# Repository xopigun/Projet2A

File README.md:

# Projet 2A — Bus CAN, groupe 69

ENSEA 2A, projet « Conception d'une Électronique Modulaire (Bus CAN) ».
Auteurs (ordre alphabétique) : Samuel GOMRI, Dylan KIATI, Hugo MATHOUX.

**Où en est le projet : [banc-can/docs/ETAT_PROJET.md](banc-can/docs/ETAT_PROJET.md).**

| Dossier | Contenu |
|---|---|
| [`banc-can/`](banc-can/README.md) | Le banc de test : firmwares des nœuds, ICD, outils PC `canbench`, cartes KiCad (adaptateur USB-CAN, carte porteuse, câblage), simulation 3D, documentation |
| `Banc de Test/` | Dossier de définition du banc (source LaTeX et PDF) |
| `ICD/` | Formulaire ICD commun aux groupes partenaires |
| `Cobot/` | Schéma du bus CAN du Cobot |
| `GANTT/` | Planning détaillé (LaTeX) |
| `Management/` | Notes de pré-cadrage, RACI, registre des risques, plannings, macroplanning |

Cloner avec les sous-modules du firmware :

```bash
git clone --recursive https://github.com/xopigun/Projet2A.git
```

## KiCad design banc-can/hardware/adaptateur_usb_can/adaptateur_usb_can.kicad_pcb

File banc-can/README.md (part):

# Banc de test CAN — G69-BANC-001

Outil interne du **groupe 69** (ENSEA 2A, projet « Conception d'une Électronique Modulaire
(Bus CAN) ») servant à valider le standard CAN commun et les ICD produits avec les groupes
partenaires.

Le banc est **générique** : aucun code n'est spécifique à un groupe partenaire, les besoins
particuliers passent par de la configuration. Les quatre projets partenaires (Cobot RMD-X,
Ecomarathon, Formula Student, MIR1000) sont traités au même niveau.

Auteurs (ordre alphabétique) : Samuel GOMRI, Dylan KIATI, Hugo MATHOUX.

**État du projet, choix abandonnés et prochaines étapes : [docs/ETAT_PROJET.md](docs/ETAT_PROJET.md).**

---

## ⚠ À faire avant la première mise sous tension

Ces deux points sont des **modifications matérielles** sur chaque Nucleo-G431KB. Les ignorer
donne des symptômes qui ressemblent à une panne et non à une erreur de montage.

1. **Retirer le cavalier HW1**, livré fermé entre `CN4` broche 5 (`D2` = PA12) et `CN4`
   broche 4 (`GND`) — UM2397 §5.1 et §6.1. PA12 est `FDCAN1_TX` : laissé à la masse, il
   place le bus en **état dominant permanent** et bloque toute communication.

2. **Souder les ponts SB9 et SB10** pour connecter le quartz 24 MHz. En sortie d'usine la
   carte démarre sur le **HSI** (UM2397 §6.5, Table 9), dont la précision de ±1 % dépasse
   plus du double la tolérance admissible de 0,485 % à 500 kbit/s. Tant que ce n'est pas
   fait, compiler avec `-DBENCH_CLOCK_SOURCE=HSI` : le firmware émet un avertissement à la
   compilation, affiche `HSI - NON VALIDE` sur l'écran et signale le défaut dans son
   heartbeat, et `canbench` refuse alors de prononcer un verdict de réussite.

**Procédure de mise en route pas à pas : [docs/bringup.md](docs/bringup.md).** Elle amène
trois cartes neuves à un bus qui communique, en validant l'horloge, le temps de bit et
l'encodage **avant** tout câblage grâce au bouclage interne du FDCAN.

Brochage, terminaisons et injection de fautes : [docs/pinout.md](docs/pinout.md).

---

## Démarrage rapide

### Prérequis

| Outil | Version | Rôle |
|---|---|---|
| git | ≥ 2.30 | sous-modules |
| CMake | ≥ 3.24 | presets version 6 |
| Ninja | ≥ 1.10 | générateur |
| `arm-none-eabi-gcc` | ≥ 12 | firmwares |
| `gcc` ou `clang` | — | tests unitaires natifs |
| Python | ≥ 3.10 | outils PC et génération depuis l'ICD |
| STM32CubeProgrammer **ou** OpenOCD | — | programmation (facultatif) |

### Cloner

```bash
git clone --recursive <url> banc-can
cd banc-can
```

Si le dépôt a été cloné sans `--recursive` :

```bash
git submodule update --init --recursive
```

### Compiler et exécuter les tests unitaires (aucun matériel)

```bash
cmake --preset host
cmake --build --preset host
ctest --preset host
```

### Compiler un firmware

Un preset par nœud : `n1` à `n4`, quatre Nucleo-G431KB.

```bash
cmake --preset n1
cmake --build --preset n1
```

### Programmer un nœud

```bash
cmake --build --preset n1 --target flash_n1
```

`STM32_Programmer_CLI` et `openocd` sont cherchés dans le `PATH` puis dans les emplacements
d'installation usuels ; le premier trouvé est utilisé. Pour forcer :
`cmake --preset n1 -DBENCH_FLASH_TOOL=openocd`.

**Plusieurs cartes branchées à la fois** : sans autre précision, l'outil programme la
première sonde trouvée, pas forcément le nœud visé. Lister les sondes, puis fixer une fois
pour toutes le numéro de série de chaque nœud :

```bash
STM32_Programmer_CLI --list st-link
```

```bash
cmake --preset n1-scope-direct -DBENCH_STLINK_SN=005000463335510433383531
```

### Installer les outils PC

```bash
python -m pip install -e "pc[dev]"
```

### Premier test, sans matériel

Toutes les sous-commandes fonctionnent sur le bus `virtual` de python-can, avec un
simulateur qui reproduit N1 à N4 (ARM/GO et heartbeat compris) :

```bash
canbench --interface virtual --simulate arbitration --cycles 100
canbench --interface virtual --simulate encoding
canbench --interface virtual --simulate faults
canbench --interface virtual --simulate busload --measure 2
```

`--simulate` démarre un simulateur reproduisant N1 à N4. **Aucun verdict de réussite n'est
prononcé sur le bus virtuel** : le simulateur reproduit le comportement attendu, il ne le
démontre pas. Les rapports produits portent la mention correspondante.

### Interface graphique

Pour une démonstration, ou simplement pour piloter le banc sans ligne de commande, il
existe un **logiciel Windows**, `BancCAN.exe`. Il s'ouvre dans sa propre fenêtre, se
connecte depuis le bouton « Connexion » (simulation ou CANable), et s'arrête quand on
ferme la fenêtre. Le bouton « Aide » explique chaque indicateur, chaque test et chaque
faute. L'exécutable n'est pas versionné ; il se reconstruit en une minute :

```bash
python -m pip install pyinstaller
```

```bash
python pc/build_exe.py
```

Le fichier produit est `dist/BancCAN.exe`. Pour que le logiciel pilote un CANable réel,
installer le pilote python-can correspondant **avant** de le construire
(`python -m pip install -e "pc[slcan]"` ou `"pc[gs-usb]"`) : il est alors embarqué.
Le firmware candleLight (`gs_usb`) demande en outre la bibliothèque système **libusb**,
absente par défaut sous Windows : installer `libusb-package` avant la construction, qui
embarque alors `libusb-1.0.dll`. Tant qu'elle manque, la fenêtre « Connexion »
l'indique au lieu de proposer une connexion vouée à l'échec. Le firmware `slcan` n'en a
pas besoin.

Sans construire l'exécutable, **double-cliquer sur `lancer_banc.bat`** donne la même
interface dans le navigateur. Le navigateur s'ouvre sur
<http://127.0.0.1:8765> et affiche le bus en direct, l'état des nœuds tiré de leurs
heartbeats, les trames décodées par l'ICD, les tests T3, T4 et T6 avec leur rapport
téléchargeable, et l'injection de fautes par `BENCH_CFG`.

Sans argument, l'interface tourne en **simulation** : un bandeau le rappelle en permanence
et aucun verdict n'y vaut preuve. Sur le banc réel :

```bash
lancer_banc.bat gs_usb
```

L'équivalent en ligne de commande est `canbench --interface virtual gui`. L'interface
n'ajoute aucune dépendance et n'a aucune logique de test propre : elle appelle les mêmes
fonctions que `canbench`.

### Premier test sur le banc réel

Le CANable 2.0 est supporté en firmware candleLight (`gs_usb`) et en `slcan` :

```bash
canbench --interface gs_usb  monitor
canbench --interface slcan --channel COM7 arbitration --cycles 1000
```

### Adaptateur ZLG USBCAN-UC12 (sans désactiver l'intégrité de la mémoire)

Le pilote noyau fourni par ZLG (`usbcan.sys`, 2017) est refusé par l'**intégrité de la
mémoire** de Windows. Le banc ne s'en sert pas : `pc/canbench/zlg_usbcan/` parle à
l'adaptateur directement, à travers **WinUSB**, le pilote générique signé par Microsoft.
Le protocole a été reconstitué pour l'interopérabilité ; il est décrit dans
[`PROTOCOLE.md`](pc/canbench/zlg_usbcan/PROTOCOLE.md).

Mise en place, une seule fois :

1. Gestionnaire de périphériques, sur l'adaptateur : *Mettre à jour le pilote* >
   *Choisir parmi la liste* > **Périphérique WinUsb**.
2. Installer les dépendances :

```bash
python -m pip install -e "pc[zlg]"
```

Ensuite :

```bash
canbench --interface zlg monitor
```

```bash
lancer_banc.bat zlg
```

Dans l'interface graphique, le panneau **Qualité** affiche alors l'état du contrôleur de
l'adaptateur (REC/TEC, error-active/warning/passive), ses événements d'erreur, les trames
émises que personne n'acquitte, et, pour chaque identifiant, la période, la gigue et les
trames manquées, mesurées sur l'horodatage matériel à 0,1 ms. Le type d'erreur CAN
(bourrage, CRC…) n'est pas disponible sur cet adaptateur. L'outil bas niveau
`python -m canbench.zlg_usbcan probe` interroge l'adaptateur sans passer par le banc.

---

## Organisation du dépôt

| Répertoire | Contenu |
|---|---|
| `icd/` | `bench_icd.yaml` — **source unique** des identifiants, signaux et encodages |
| `tools/codegen/` | génération depuis l'ICD : C, Python, DBC, LaTeX |
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
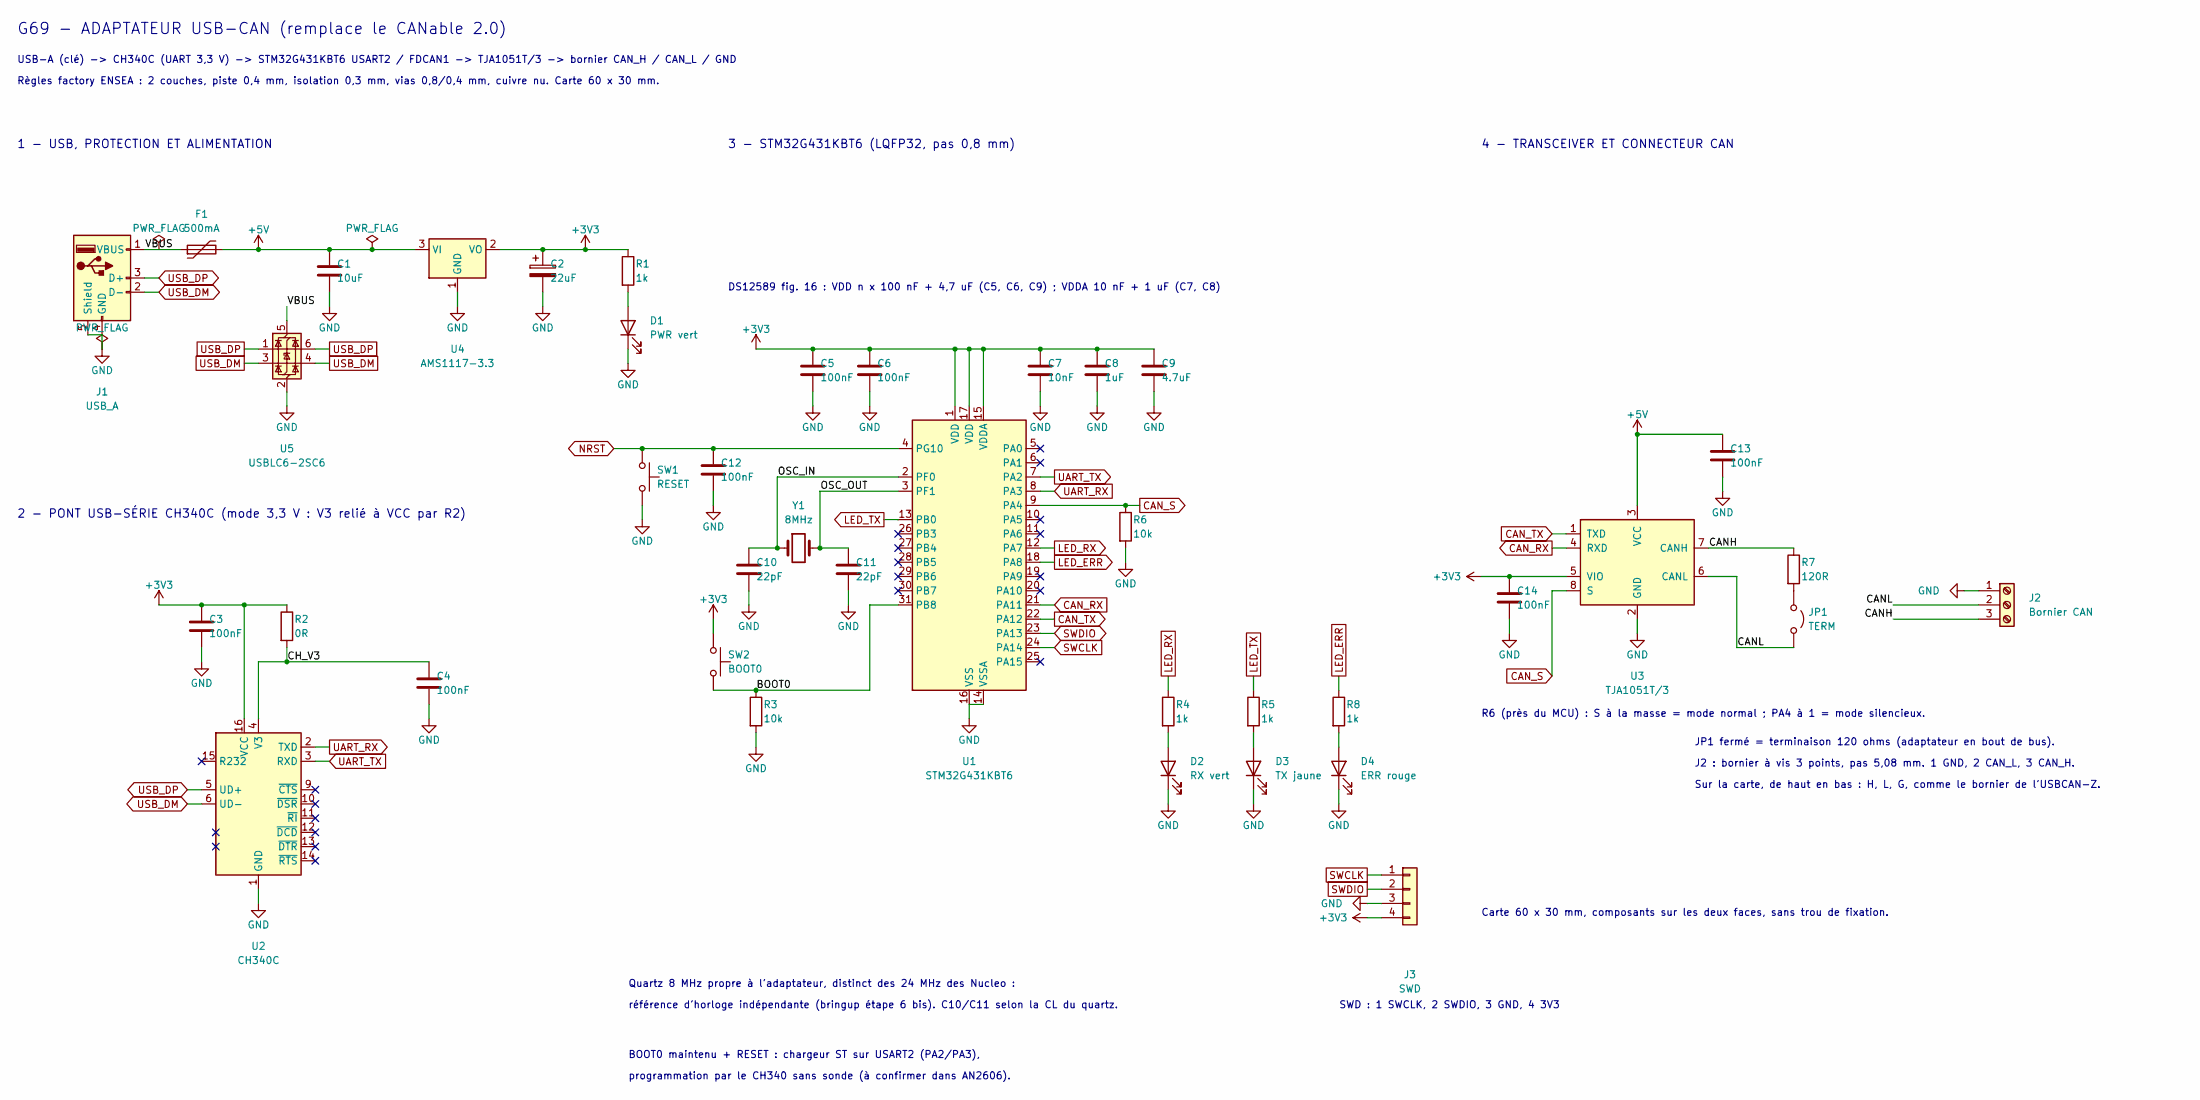
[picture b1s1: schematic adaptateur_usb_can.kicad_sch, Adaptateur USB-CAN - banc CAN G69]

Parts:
C1: 10uF; C_0805_2012Metric_Pad1.18x1.45mm_HandSolder; MPN CL21A106KOQNNNE
C2: 22uF; CP_EIA-3216-18_Kemet-A_HandSolder; MPN T491A226K010AT
C3, C4, C5, C6, C12, C13, C14: 100nF; C_0805_2012Metric_Pad1.18x1.45mm_HandSolder; MPN CL21B104KBCNNNC
C7: 10nF; C_0805_2012Metric_Pad1.18x1.45mm_HandSolder; MPN CL21B103KBANNNC
C8: 1uF; C_0805_2012Metric_Pad1.18x1.45mm_HandSolder; MPN CL21B105KOFNNNE
C9: 4.7uF; C_0805_2012Metric_Pad1.18x1.45mm_HandSolder; MPN CL21A475KAQNNNE
C10, C11: 22pF; C_0805_2012Metric_Pad1.18x1.45mm_HandSolder; MPN CL21C220JBANNNC
D1: PWR vert; LED_0805_2012Metric_Pad1.15x1.40mm_HandSolder; MPN 150080GS75000
D2: RX vert; LED_0805_2012Metric_Pad1.15x1.40mm_HandSolder; MPN 150080GS75000
D3: TX jaune; LED_0805_2012Metric_Pad1.15x1.40mm_HandSolder; MPN 150080YS75000
D4: ERR rouge; LED_0805_2012Metric_Pad1.15x1.40mm_HandSolder; MPN 150080RS75000
F1: 500mA; Fuse_1206_3216Metric_Pad1.42x1.75mm_HandSolder; MPN MF-NSMF050-2
J1: USB_A; USB_A_CNCTech_1001-011-01101_Horizontal_PercagesENSEA; MPN 1001-011-01101
J2: Bornier CAN; TerminalBlock_Phoenix_MKDS-1,5-3-5.08_1x03_P5.08mm_Horizont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; MPN 1729131 (MKDS 1,5/ 3-5,08)
J3: SWD; PinHeader_1x04_P2.54mm_Vertical; MPN 61300411121
JP1: TERM; PinHeader_1x02_P2.54mm_Vertical; MPN 61300211121
R1, R4, R5, R8: 1k; R_0805_2012Metric_Pad1.20x1.40mm_HandSolder; MPN RC0805FR-071KL
R2: 0R; R_0805_2012Metric_Pad1.20x1.40mm_HandSolder; MPN RC0805JR-070RL
R3, R6: 10k; R_0805_2012Metric_Pad1.20x1.40mm_HandSolder; MPN RC0805FR-0710KL
R7: 120R; R_0805_2012Metric_Pad1.20x1.40mm_HandSolder; MPN RC0805FR-07120RL
SW1: RESET; SW_SPST_B3U-1000P; MPN B3U-1000P
SW2: BOOT0; SW_SPST_B3U-1000P; MPN B3U-1000P
U1: STM32G431KBT6; LQFP-32_7x7mm_P0.8mm; MPN STM32G431KBT6
U2: CH340C; SOIC-16_3.9x9.9mm_P1.27mm; MPN CH340C
U3: TJA1051T/3; SOIC-8_3.9x4.9mm_P1.27mm; MPN TJA1051T/3,118
U4: AMS1117-3.3; SOT-223-3_TabPin2; MPN AMS1117-3.3
U5: USBLC6-2SC6; SOT-23-6; MPN USBLC6-2SC6
Y1: 8MHz; Crystal_SMD_5032-2Pin_5.0x3.2mm_Pastilles2.6mm; MPN quartz 8 MHz 5032, CL 16 pF (C10/C11 = 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

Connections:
+3V3: C2.1, C3.1, C5.1, C6.1, C7.1, C8.1, C9.1, C14.1, J3.4, R1.1, R2.1, SW2.1, U1.1 (VDD), U1.15 (VDDA), U1.17 (VDD), U2.16 (VCC), U3.5 (VIO), U4.2 (VO)
+5V: C1.1, C13.1, F1.2, U3.3 (VCC), U4.3 (VI)
/BOOT0: R3.1, SW2.2, U1.31 (PB8)
/CANH: J2.3, R7.1, U3.7 (CANH)
/CANL: J2.2, JP1.2 (B), U3.6 (CANL)
/CH_V3: C4.1, R2.2, U2.4 (V3)
/OSC_IN: C10.1, U1.2 (PF0), Y1.1
/OSC_OUT: C11.1, U1.3 (PF1), Y1.2
/VBUS: F1.1, J1.1 (VBUS), U5.5 (VBUS)
CAN_RX: U1.21 (PA11), U3.4 (RXD)
CAN_S: R6.1, U1.9 (PA4), U3.8 (S)
CAN_TX: U1.22 (PA12), U3.1 (TXD)
GND: C1.2, C2.2, C3.2, C4.2, C5.2, C6.2, C7.2, C8.2, C9.2, C10.2, C11.2, C12.2, C13.2, C14.2, D1.1 (K), D2.1 (K), D3.1 (K), D4.1 (K), J1.4 (GND), J1.5 (Shield), J2.1, J3.3, R3.2, R6.2, SW1.2, U1.14 (VSSA), U1.16 (VSS), U1.32 (VSS), U2.1 (GND), U3.2 (GND), U4.1 (GND), U5.2 (GND)
LED_ERR: R8.1, U1.18 (PA8)
LED_RX: R4.1, U1.12 (PA7)
LED_TX: R5.1, U1.13 (PB0)
NRST: C12.1, SW1.1, U1.4 (PG10)
unnamed: D1.2 (A), R1.2
unnamed: D2.2 (A), R4.2
unnamed: D3.2 (A), R5.2
unnamed: D4.2 (A), R8.2
unnamed: JP1.1 (A), R7.2
SWCLK: J3.1, U1.24 (PA14)
SWDIO: J3.2, U1.23 (PA13)
UART_RX: U1.8 (PA3), U2.2 (TXD)
UART_TX: U1.7 (PA2), U2.3 (RXD)
USB_DM: J1.2 (D-), U2.6 (UD-), U5.3 (I/O2), U5.4 (I/O2)
USB_DP: J1.3 (D+), U2.5 (UD+), U5.1 (I/O1), U5.6 (I/O1)

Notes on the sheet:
G69 - ADAPTATEUR USB-CAN (remplace le CANable 2.0)
USB-A (clé) -> CH340C (UART 3,3 V) -> STM32G431KBT6 USART2 / FDCAN1 -> TJA1051T/3 -> bornier CAN_H / CAN_L / GND
Règles factory ENSEA : 2 couches, piste 0,4 mm, isolation 0,3 mm, vias 0,8/0,4 mm, cuivre nu. Carte 60 x 30 mm.
1 - USB, PROTECTION ET ALIMENTATION
2 - PONT USB-SÉRIE CH340C (mode 3,3 V : V3 relié à VCC par R2)
3 - STM32G431KBT6 (LQFP32, pas 0,8 mm)
DS12589 fig. 16 : VDD n x 100 nF + 4,7 uF (C5, C6, C9) ; VDDA 10 nF + 1 uF (C7, C8)
Quartz 8 MHz propre à l'adaptateur, distinct des 24 MHz des Nucleo :
référence d'horloge indépendante (bringup étape 6 bis). C10/C11 selon la CL du quartz.
BOOT0 maintenu + RESET : chargeur ST sur USART2 (PA2/PA3),
programmation par le CH340 sans sonde (à confirmer dans AN2606).
SWD : 1 SWCLK, 2 SWDIO, 3 GND, 4 3V3
4 - TRANSCEIVER ET CONNECTEUR CAN
R6 (près du MCU) : S à la masse = mode normal ; PA4 à 1 = mode silencieux.
JP1 fermé = terminaison 120 ohms (adaptateur en bout de bus).
J2 : bornier à vis 3 points, pas 5,08 mm. 1 GND, 2 CAN_L, 3 CAN_H.
Sur la carte, de haut en bas : H, L, G, comme le bornier de l'USBCAN-Z.
Carte 60 x 30 mm, composants sur les deux faces, sans trou de fixation.

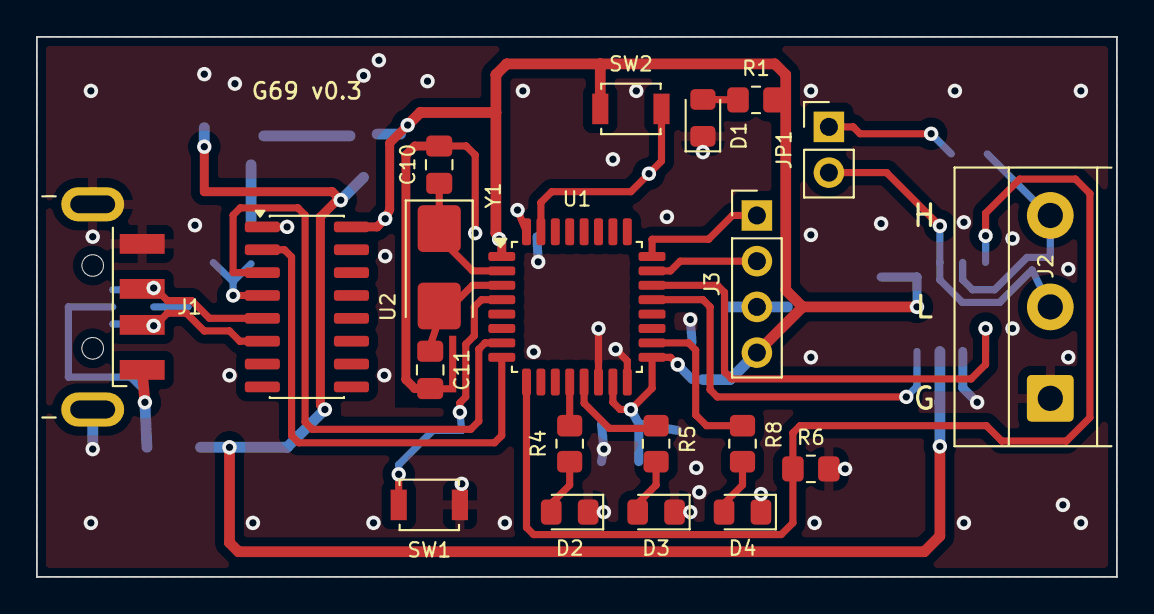
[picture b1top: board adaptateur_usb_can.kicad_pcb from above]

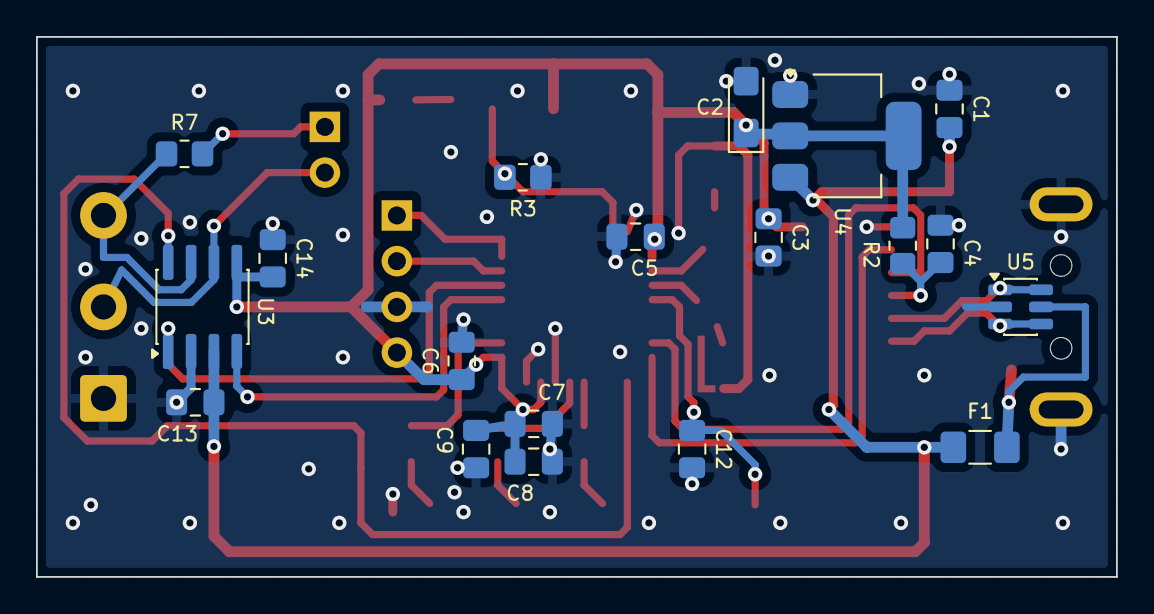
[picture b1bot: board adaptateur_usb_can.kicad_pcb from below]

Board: 2 copper layers, 60.0 x 30.0 mm, 39 parts (19 on the bottom side), 28 nets.

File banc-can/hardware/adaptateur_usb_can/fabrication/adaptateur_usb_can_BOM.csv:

Qté;Repères;Désignation;Valeur;Boîtier;Remarque
1;C1;Condensateur céramique X5R 16 V;10uF;0805;entrée 5 V du régulateur
2;C10, C11;Condensateur céramique C0G/NP0 50 V;22pF;0805;à ajuster selon la CL du quartz
1;C2;Condensateur tantale solide 22 µF 10 V, boîtier A (3216-18), polarisé;22uF;tantale A (3216);sortie de l'AMS1117 : tantale exigé pour la stabilité
7;C3, C4, C5, C6, C12, C13, C14;Condensateur céramique X7R 50 V;100nF;0805;découplage
1;C7;Condensateur céramique X7R 50 V;10nF;0805;VDDA, avec C8
1;C8;Condensateur céramique X7R 16 V;1uF;0805;VDDA
1;C9;Condensateur céramique X5R 10 V;4.7uF;0805;réservoir 3,3 V
1;D1;LED verte;PWR vert;0805;
1;D2;LED verte;RX vert;0805;
1;D3;LED jaune;TX jaune;0805;
1;D4;LED rouge;ERR rouge;0805;LED d'erreur, sur PA8
1;F1;Fusible réarmable PTC, 500 mA maintenu, 6 V mini;500mA;1206;
1;J1;Fiche USB type A mâle coudée, pour CI (CNCTech 1001-011-01101);USB_A;traversant;branchement direct sur le PC
1;J2;Bornier à vis 3 points, pas 5,08 mm, pour CI (type Phoenix MKDS 1,5/3-5,08);Bornier CAN;traversant;bus CAN : H, L, G
1;J3;Barrette mâle sécable 1 × 4, pas 2,54 mm;SWD;traversant;SWCLK, SWDIO, GND, 3V3
1;JP1;Barrette mâle 1 × 2, pas 2,54 mm + cavalier;TERM;traversant;terminaison 120 Ω
4;R1, R4, R5, R8;Résistance 1 %, 1/8 W;1k;0805;
1;R2;Résistance 0 Ω (ou strap);0R;0805;CH340C en mode 3,3 V
2;R3, R6;Résistance 1 %, 1/8 W;10k;0805;
1;R7;Résistance 1 %, 1/8 W;120R;0805;terminaison CAN
1;SW1;Bouton poussoir CMS 3 × 2,5 mm (Omron B3U-1000P);RESET;B3U;face avant
1;SW2;Bouton poussoir CMS 3 × 2,5 mm (Omron B3U-1000P);BOOT0;B3U;face avant
1;U1;Microcontrôleur STM32G431KBT6, LQFP32;STM32G431KBT6;LQFP-32;pas 0,8 mm
1;U2;Pont USB-UART CH340C, SOIC-16;CH340C;SOIC-16;version C : sans quartz externe
1;U3;Transceiver CAN TJA1051T/3, SOIC-8;TJA1051T/3;SOIC-8;suffixe /3 : broche VIO
1;U4;Régulateur linéaire 3,3 V AMS1117-3.3, SOT-223;AMS1117-3.3;SOT-223;
1;U5;Protection ESD USB USBLC6-2SC6, SOT-23-6;USBLC6-2SC6;SOT-23-6;
1;Y1;Quartz 8 MHz CMS 5 × 3,2 mm, 2 pastilles;8MHz;5032;noter sa capacité de charge CL

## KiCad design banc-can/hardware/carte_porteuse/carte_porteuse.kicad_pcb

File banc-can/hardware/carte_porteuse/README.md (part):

# Carte porteuse d'un nœud du banc CAN (v0.4)

Une Nucleo-G431KB s'enfiche dessus. La carte porte le transceiver TJA1051T/3 et ses
découplages, un bornier qui raccorde le nœud au bus, la terminaison 120 Ω sur cavalier,
l'écran OLED, le MPU-6050 (N2) et deux LED d'état.
Plus aucun fil Dupont. À fabriquer en 4 exemplaires.

**v0.4 (25/11/2026)** : routage repris après les remarques du cours d'électronique, sans
changer le schéma, le contour, les fixations ni la place des connecteurs. Le TJA1051 est monté
de 8 mm vers le bornier et tourné d'un quart de tour : CANH et CANL vont au bornier côte à
côte sur la face avant, sans via, en 15 mm (31 et 25 mm sur deux faces avant). La face
arrière redevient un plan de masse d'un seul tenant (28 mm de pistes en cinq ponts au lieu
de 245 mm), relié à la face avant par 43 vias au lieu de 9. Le routage est écrit en
coordonnées dans `router_manuel.py` ; Freerouting n'est plus utilisé. Le bornier est percé à
1,4 mm (pas de la factory), une lettre H, L, G repère chaque borne, et rien d'autre que la
masse ne passe à moins de 1 mm des têtes de vis. Le schéma n'a pas changé électriquement ;
son cartouche et `fabrication/schema.pdf` passent en révision 0.4 pour suivre la carte.

**v0.3 (24/11/2026)** : un seul bornier au lieu de deux. Avec une entrée et une sortie sur
chaque carte, la paire torsadée était coupée et détorsadée à chaque nœud, et le bus
traversait les quatre cartes. Le nœud est maintenant une branche courte, torsadée jusqu'au
bornier, qui rejoint un point de jonction commun (voir « Raccordement au bus »). Le coin
arrière gauche libéré a été retiré.

## Disposition (vue de dessus, arrière en haut)

| Zone | Contenu |
|---|---|
| Bande arrière | bornier du bus à droite (fils vers la droite), fixation M3 H1 |
| Colonne centrale | barrettes de la Nucleo, posée dans la profondeur, **USB vers l'arrière** (câble vers le hub) ; sous elle, le TJA1051 en haut, tourné vers le bornier, ses 100 nF, les résistances et la fixation H2 ; barrette coudée de l'OLED au bord avant |
| Gauche | barrette coudée du MPU-6050 : le module tient debout au-delà du bord |
| Droite | cavalier TERM, LED **B** (bus-off, jaune) et **E** (erreur, rouge) |

Contour en escalier : 1 830 mm² au lieu de 3 250 mm² pour la v0.1 rectangulaire (−44 %).

## Raccordement au bus

Le bus est une « pieuvre » : chaque nœud et le ZLG USBCAN-UC12 sont reliés par une branche
courte à un point de jonction commun, fait de **trois bornes Wago 221-420** (10 entrées à
leviers, toutes reliées entre elles) : une pour CAN_H, une pour CAN_L, une pour la masse.
Cinq entrées sont prises par ligne (ZLG et N1 à N4), cinq restent libres pour un nœud
partenaire ou une sonde.

- Chaque branche arrive sur le bornier J1 : de l'arrière vers l'avant **H, L, G**
  (une lettre en face de chaque borne, contre le dos du bornier, côté Nucleo).
- Fil souple de câblage en trois couleurs, de 0,2 à 0,5 mm² : CAN_H et CAN_L torsadés
  ensemble à la main (un tour tous les 1 à 2 cm) du Wago jusqu'au bornier, la masse à côté.
  Le bornier MKDS 1,5 est donné pour 0,2 à 2,5 mm² et le Wago 221-420 pour 0,14 à 4 mm² en
  fil souple ; un fil Dupont (0,08 à 0,13 mm²) est trop fin pour les deux.
- C'est une étoile et non une ligne : garder les branches courtes (≤ 0,3 m) et de longueurs
  proches.
- Deux terminaisons de 120 Ω seulement : l'interrupteur du ZLG et le cavalier TERM de N4
  (câblé vers SW1). Pas de cavalier sur N1, N2 et N3.
- Contrôle hors tension : environ 60 Ω entre CAN_H et CAN_L ([pinout.md](../../docs/pinout.md) §6).

À commander pour le banc : 3 Wago 221-420 et du fil souple en trois couleurs.

## Montage

1. Souder les CMS dans cet ordre : **U1 d'abord**, puis C1, C2 et R7 qui l'entourent (C1 est
   à 0,9 mm des pattes 1 à 4 de U1 : contrôler à la loupe qu'aucun pont ne les relie), puis
   R1, R2, R3, R9, R10, D1, D2. Ensuite seulement les barrettes et le bornier : U1, C1, C2 et
   R7 sont entre les barrettes et le bornier, le fer n'y passe plus après. Le cuivre est nu :
   après soudure, vérifier à la loupe l'absence de pont entre les pastilles de CN3/CN4 et les
   pistes qui les longent (0,37 mm au plus serré).
2. R9 et R10 (0 Ω) alimentent l'OLED, dont les broches sont dans l'ordre GND, VCC, SCL, SDA
   (modules reçus). Les variantes R11/R12 (OLED en VCC/GND) et la barrette capteurs J8 ont été
   retirées le 17/11/2026.
3. Visser la carte sur la plaque du banc (H1, H2, vis M3 à tête de 5,5 mm, sans rondelle
   métallique plus large : la tête repose sur le plan de masse, et les pistes les plus proches
   sont à 1,05 mm de la tête de H1 et 1,47 mm de celle de H2), **puis** enficher la Nucleo :
   broche 1 de CN3 et CN4 côté USB, flèche « ^ USB ».
4. L'OLED s'enfiche à l'horizontale dans sa barrette coudée et tient debout, à l'envers :
   le firmware retourne l'affichage. Le MPU-6050 de même, sur N2.
5. Cavalier TERM sur le nœud en bout de ligne seulement (N4 : câble vers l'interrupteur SW1).

Non montés : R8 (S sur PB6), R4/R5 (tirages I2C, les modules ont les leurs). PA4 et PA7
(capteurs Hall et 1-Wire, reportés) restent libres sur la Nucleo.

## Vérifications

**Électrique** : ERC 0 ; DRC 0 erreur, 0 liaison manquante, 0 écart avec le schéma. Restent
60 avertissements, tous voulus : 59 pour les contours des barrettes coudées et du bornier, qui
dépassent le bord de la carte, et 1 parce que le bornier J1 est percé à 1,4 mm au lieu des
1,3 mm de sa bibliothèque. Plus aucun repère sur une pastille ni sur un autre tracé.
`verifier_criteres.py` relance l'ERC et le DRC et contrôle les critères ci-dessous.

**Routage** (mesuré par `verifier_criteres.py`) :

| Critère | Sur la carte |
|---|---|
| Vias de masse | 43 vias GND (49 vias en tout), grille en quinconce de 6 mm ; aucun cuivre de masse à plus de 7,4 mm d'un via ; un via à 1,2 mm de C1 (entre C1 et la broche GND de U1) et 1,3 mm de C2 |
| Plan de masse | face arrière d'un seul tenant (77 % de la carte), 28 mm de pistes en cinq ponts (SDA 10,4 ; CAN_S 7,9 ; SCL 3,9 ; +5V 3,2 ; CAN_TX 2,4), rien sous U1 ni sous la paire CAN ; face avant : chaque îlot de masse a son via |
| Paire CAN | U1 → bornier sur la face avant, sans via : CANH 14,9 mm, CANL 14,6 mm, côte à côte à 0,35 mm sur 11 mm. Les branches de la terminaison (R1, cavalier) partent des bornes : 16 et 12 mm de plus, imposés par la place du cavalier, qui doit rester accessible Nucleo enfichée |
| Découplage | C1 à 2,7 mm de VCC, C2 à 1,9 mm de VIO |
| Têtes de vis | disque de 7 mm interdit aux pistes et aux vias autour de H1 et H2 (règle du DRC) ; cuivre hors masse le plus proche : 1,05 mm de la tête de H1 (+3V3), 1,47 mm de celle de H2 (SDA) |
| Perçages | 0,4 mm (vias), 1,0 mm (barrettes), 1,4 mm (bornier), 3,2 mm (fixations, valeur du guide de la factory) |

Les cinq ponts de la face arrière sont imposés par le brochage. CN4 et la barrette du MPU-6050
présentent SCL, SDA et INT dans l'ordre inverse : INT passe entre les deux barrettes sur la
face avant, SDA sur la face arrière, SCL fait le tour par le nord de CN4. CAN_TX, CAN_S et
CAN_RX descendent le long de CN4 alors que l'I2C en repart vers l'OLED : SCL et SDA quittent
leur pastille de CN4 par l'arrière, sur 3,9 mm, et CAN_TX y entre de même. CAN_S (option non
montée, R8) passe sous le +3V3 du MPU-6050 par un pont de 7,9 mm, à 2,7 mm des pattes de U1.

Quatre vias de masse sont sous un corps de composant, faute d'autre place à moins de 8 mm :
trois sous la barrette du MPU-6050, dont le corps couvre toute l'aile gauche, et un sous le
bornier. La factory métallise les vias, ils affleurent. S'il fallait un jour les riveter ou
les étamer, retirer ces quatre-là (`coudre_gnd.py` et `verifier_criteres.py` en donnent la
liste) : le cuivre de masse le plus éloigné d'un via serait alors à 14 mm, dans le coin de l'aile gauche.

Le +5V arrive sur la pastille de la broche VCC de U1 par le canal sous le boîtier, et C1 est
branché à l'autre bout de cette pastille, 0,9 mm plus loin. Faire arriver le +5V d'abord sur
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
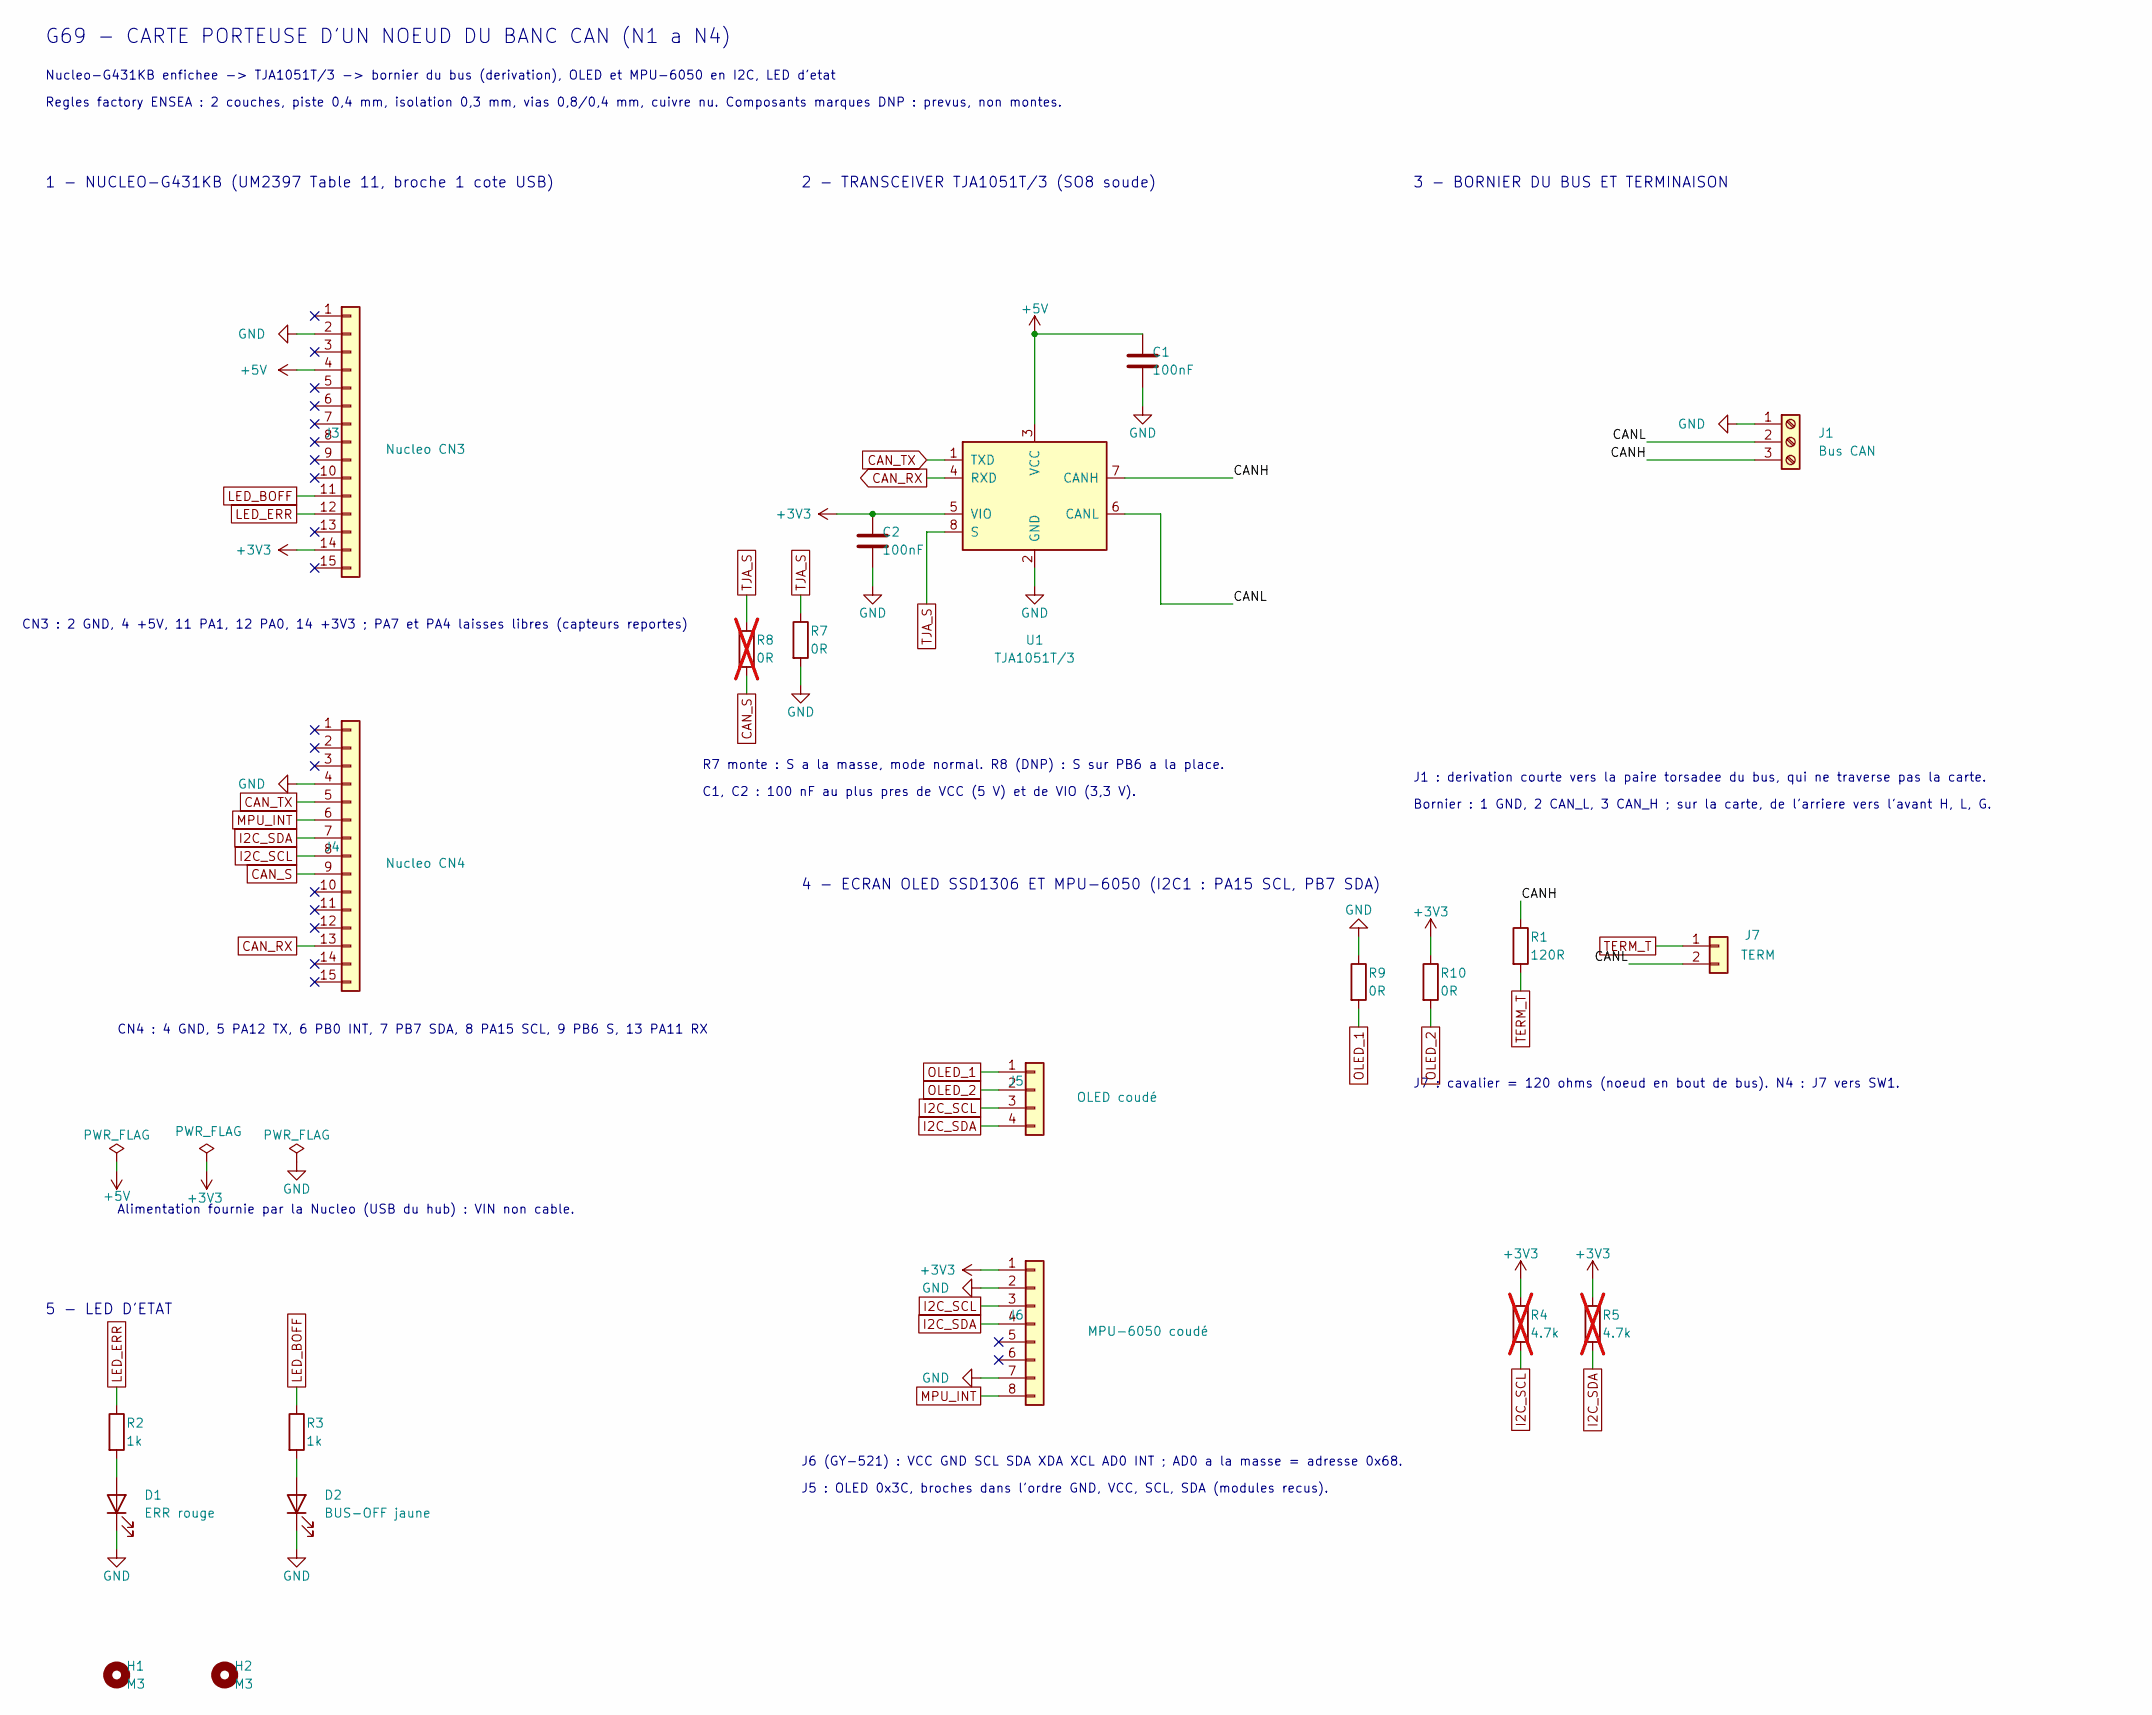
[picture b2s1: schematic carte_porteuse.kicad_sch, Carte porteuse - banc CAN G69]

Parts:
C1, C2: 100nF; C_0805_2012Metric_Pad1.18x1.45mm_HandSolder; MPN CL21B104KBCNNNC
D1: ERR rouge; LED_0805_2012Metric_Pad1.15x1.40mm_HandSolder; MPN 150080RS75000
D2: BUS-OFF jaune; LED_0805_2012Metric_Pad1.15x1.40mm_HandSolder; MPN 150080YS75000
H1, H2: M3; MountingHole_3.2mm_M3; MPN trou de fixation 3,2 mm, vis M3
J1: Bus CAN; TerminalBlock_Phoenix_MKDS-1,5-3-5.08_1x03_P5.08mm_Horizont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; MPN 1729131 (MKDS 1,5/ 3-5,08)
J3: Nucleo CN3; PinSocket_1x15_P2.54mm_Vertical; MPN barrette femelle 1 x 15, pas 2,54 mm
J4: Nucleo CN4; PinSocket_1x15_P2.54mm_Vertical; MPN barrette femelle 1 x 15, pas 2,54 mm
J5: OLED coudé; PinSocket_1x04_P2.54mm_Horizontal; MPN barrette femelle coudée 1 x 4, pas 2,54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
J6: MPU-6050 coudé; PinSocket_1x08_P2.54mm_Horizontal; MPN barrette femelle coudée 1 x 8, pas 2,54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
J7: TERM; PinHeader_1x02_P2.54mm_Vertical; MPN 61300211121
R1: 120R; R_0805_2012Metric_Pad1.20x1.40mm_HandSolder; MPN RC0805FR-07120RL
R2, R3: 1k; R_0805_2012Metric_Pad1.20x1.40mm_HandSolder; MPN RC0805FR-071KL
R4, R5: 4.7k; R_0805_2012Metric_Pad1.20x1.40mm_HandSolder; MPN RC0805FR-074K7L; not fitted
R7, R9, R10: 0R; R_0805_2012Metric_Pad1.20x1.40mm_HandSolder; MPN RC0805JR-070RL
R8: 0R; R_0805_2012Metric_Pad1.20x1.40mm_HandSolder; MPN RC0805JR-070RL; not fitted
U1: TJA1051T/3; SOIC-8_3.9x4.9mm_P1.27mm; MPN TJA1051T/3,118

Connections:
+3V3: C2.1, J3.14, J6.1, R4.1, R5.1, R10.1, U1.5 (VIO)
+5V: C1.1, J3.4, U1.3 (VCC)
/CANH: J1.3, R1.1, U1.7 (CANH)
/CANL: J1.2, J7.2, U1.6 (CANL)
CAN_RX: J4.13, U1.4 (RXD)
CAN_S: J4.9, R8.2
CAN_TX: J4.5, U1.1 (TXD)
GND: C1.2, C2.2, D1.1 (K), D2.1 (K), J1.1, J3.2, J4.4, J6.2, J6.7, R7.2, R9.1, U1.2 (GND)
I2C_SCL: J4.8, J5.3, J6.3, R4.2
I2C_SDA: J4.7, J5.4, J6.4, R5.2
LED_BOFF: J3.11, R3.1
LED_ERR: J3.12, R2.1
MPU_INT: J4.6, J6.8
unnamed: D1.2 (A), R2.2
unnamed: D2.2 (A), R3.2
OLED_1: J5.1, R9.2
OLED_2: J5.2, R10.2
TERM_T: J7.1, R1.2
TJA_S: R7.1, R8.1, U1.8 (S)

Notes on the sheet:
4 - ECRAN OLED SSD1306 ET MPU-6050 (I2C1 : PA15 SCL, PB7 SDA)
J6 (GY-521) : VCC GND SCL SDA XDA XCL AD0 INT ; AD0 a la masse = adresse 0x68.
5 - LED D'ETAT
R7 monte : S a la masse, mode normal. R8 (DNP) : S sur PB6 a la place.
J5 : OLED 0x3C, broches dans l'ordre GND, VCC, SCL, SDA (modules recus).
Alimentation fournie par la Nucleo (USB du hub) : VIN non cable.
J1 : derivation courte vers la paire torsadee du bus, qui ne traverse pas la carte.
Regles factory ENSEA : 2 couches, piste 0,4 mm, isolation 0,3 mm, vias 0,8/0,4 mm, cuivre nu. Composants marques DNP : prevus, non montes.
Bornier : 1 GND, 2 CAN_L, 3 CAN_H ; sur la carte, de l'arriere vers l'avant H, L, G.
CN3 : 2 GND, 4 +5V, 11 PA1, 12 PA0, 14 +3V3 ; PA7 et PA4 laisses libres (capteurs reportes)
CN4 : 4 GND, 5 PA12 TX, 6 PB0 INT, 7 PB7 SDA, 8 PA15 SCL, 9 PB6 S, 13 PA11 RX
C1, C2 : 100 nF au plus pres de VCC (5 V) et de VIO (3,3 V).
3 - BORNIER DU BUS ET TERMINAISON
1 - NUCLEO-G431KB (UM2397 Table 11, broche 1 cote USB)
G69 - CARTE PORTEUSE D'UN NOEUD DU BANC CAN (N1 a N4)
2 - TRANSCEIVER TJA1051T/3 (SO8 soude)
J7 : cavalier = 120 ohms (noeud en bout de bus). N4 : J7 vers SW1.
Nucleo-G431KB enfichee -> TJA1051T/3 -> bornier du bus (derivation), OLED et MPU-6050 en I2C, LED d'etat

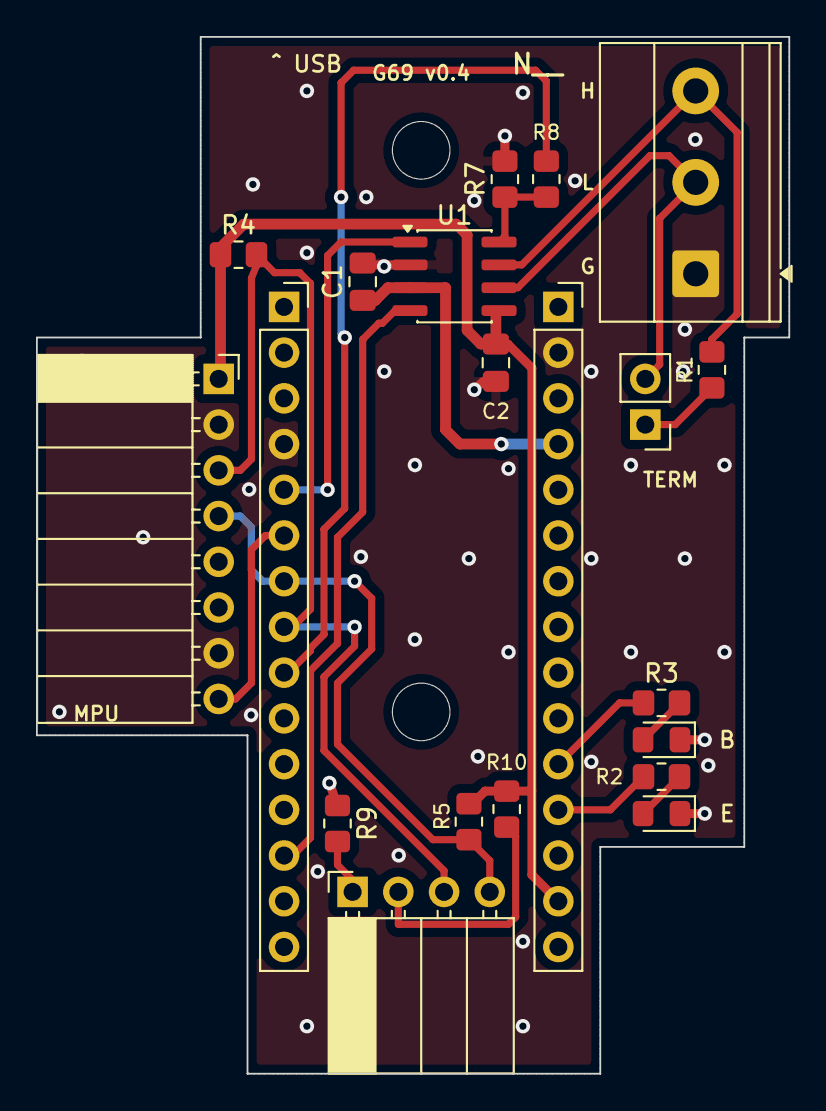
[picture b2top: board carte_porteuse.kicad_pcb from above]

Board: 2 copper layers, 41.8 x 57.6 mm, 22 parts (0 on the bottom side), 19 nets.

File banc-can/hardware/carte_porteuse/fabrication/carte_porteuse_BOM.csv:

Qté;Repères;Désignation;Valeur;Boîtier;Remarque
2;C1, C2;Condensateur céramique X7R 50 V;100nF;0805;découplage VCC et VIO du transceiver
1;D1;LED rouge;ERR rouge;0805;error-passive
1;D2;LED jaune;BUS-OFF jaune;0805;bus-off
1;J1;Bornier à vis 3 points, pas 5,08 mm (type Phoenix MKDS 1,5/3-5,08);Bus CAN;traversant;dérivation vers la paire torsadée du bus : H, L, G
1;J3;Barrette femelle 1 x 15, pas 2,54 mm;Nucleo CN3;traversant;reçoit la Nucleo-G431KB
1;J4;Barrette femelle 1 x 15, pas 2,54 mm;Nucleo CN4;traversant;reçoit la Nucleo-G431KB
1;J5;Barrette femelle coudée 1 x 4, pas 2,54 mm;OLED coudé;traversant;"écran OLED SSD1306 0,96"" debout au bord avant"
1;J6;Barrette femelle coudée 1 x 8, pas 2,54 mm;MPU-6050 coudé;traversant;module GY-521 debout au bord gauche, N2 seulement
1;J7;Barrette mâle 1 x 2, pas 2,54 mm + cavalier;TERM;traversant;"terminaison 120 ohms ; sur N4, câblée vers SW1"
1;R1;Résistance 1 %, 1/8 W;120R;0805;terminaison CAN, active avec un cavalier sur TERM
2;R2, R3;Résistance 1 %, 1/8 W;1k;0805;LED
3;R7, R9, R10;Résistance 0 ohm (ou strap);0R;0805;"R7 : broche S à la masse ; R9, R10 : alimentation de l'OLED (GND, VCC)"
1;U1;Transceiver CAN TJA1051T/3, SOIC-8;TJA1051T/3;SOIC-8;suffixe /3 : broche VIO (3,3 V)

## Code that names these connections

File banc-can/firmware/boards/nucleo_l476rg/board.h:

/**
 * @file board.h
 * @brief Affectation des broches et de l'horloge — Nucleo-L476RG (MB1136), pont CAN-USB.
 *
 * Cette carte n'est pas un nœud du banc : elle sert d'**adaptateur** entre le bus
 * et le PC (`entry/slcan_bridge.c`, protocole slcan sur le port COM virtuel du
 * ST-LINK), à la place d'un CANable. Le STM32L476RG possède un bxCAN, le même
 * type de contrôleur que le F103 du nœud N4.
 *
 * Sources : UM1724 (Nucleo-64) et DS10198 (STM32L476xx). Ce qui n'a pas été
 * relu dans ces documents est marqué `TODO(verif)`.
 *
 * Connexions au bus :
 *
 *  | Signal  | Broche | Connecteur morpho    | Remarque                         |
 *  |---------|--------|----------------------|----------------------------------|
 *  | CAN1_RX | PA11   | CN10 broche 14       | AF9                              |
 *  | CAN1_TX | PA12   | CN10 broche 12       | AF9                              |
 *  | GND     | -      | CN10 broche 9 ou 20  | masse commune avec le bus        |
 *
 * `TODO(verif)` : numéros de broches de CN10 à confirmer dans UM1724 Table 19
 * avant câblage. PA11 et PA12 ne sont pas reliées au connecteur USB de la carte
 * (l'USB du L476 n'est pas utilisé), donc sans conflit.
 */

#ifndef BENCH_BOARD_H
#define BENCH_BOARD_H

#include "stm32l4xx_hal.h"

#define BENCH_BOARD_NAME "Nucleo-L476RG"

/* -------------------------------------------------------------------- horloge
 * HSE = 8 MHz fournis par le ST-LINK (broche MCO), configuration d'usine de la
 * carte (`TODO(verif)` : UM1724 §6.7, SB50/SB54/SB55). L'horloge est alors celle
 * d'un quartz ; si elle est absente, bench_clock_config() retombe sur le HSI16 et
 * le pont l'annonce (HSI non valide pour juger un débit).
 *
 * PLL : (8 MHz / 1) x 20 / 2 = 80 MHz. HSI : (16 MHz / 2) x 20 / 2 = 80 MHz.
 */
#define BENCH_HSE_HZ 8000000u
#define BENCH_HSI_HZ 16000000u

#define BENCH_SYSCLK_HZ 80000000u
#define BENCH_PCLK1_HZ  80000000u  /**< horloge du bxCAN */

/* ------------------------------------------------------------ temps de bit
 * 500 kbit/s : 80 MHz / 10 = 8 MHz, soit 16 quanta de 125 ns, point
 * d'échantillonnage à (1 + 13) / 16 = 87,5 % — le même que sur les autres
 * cartes. Les autres débits slcan (S0 à S8) gardent 16 quanta et changent le
 * prédiviseur : voir slcan_bridge.c.
 */
/** Prédiviseur de 500 kbit/s ; les autres débits slcan le recalculent (slcan_bridge.c). */
#define BENCH_CAN_PRESCALER 10u
#define BENCH_CAN_TSEG1 13u
#define BENCH_CAN_TSEG2 2u
#define BENCH_CAN_SJW   2u
#define BENCH_CAN_TQ_PER_BIT 16u

/* -------------------------------------------------------------------- CAN */
#define BENCH_CAN_RX_PORT GPIOA
#define BENCH_CAN_RX_PIN  GPIO_PIN_11
#define BENCH_CAN_TX_PORT GPIOA
#define BENCH_CAN_TX_PIN  GPIO_PIN_12
#define BENCH_CAN_AF      GPIO_AF9_CAN1

/** Pas de broche S de transceiver sur cette carte. */
#define BENCH_HAS_TRANSCEIVER_STANDBY 0

/* -------------------------------------------------------------------- LED */
/** LD2 (verte) = PA5 (UM1724 §6.5). Clignote à chaque trame transmise au PC. */
#define BENCH_LED_PORT GPIOA
#define BENCH_LED_PIN  GPIO_PIN_5
#define BENCH_LED_CLK_ENABLE() __HAL_RCC_GPIOA_CLK_ENABLE()
#define BENCH_LED_PULSE_MS 20u

/* ----------------------------------------------------- liaison avec le PC
 * Port COM virtuel du ST-LINK : USART2 sur PA2 (TX) et PA3 (RX), AF7 (UM1724
 * §6.8). C'est le canal slcan : rien d'autre ne doit y écrire (pas de printf).
 */
#define BENCH_HAS_SERIAL_LOG 0
#define BENCH_UART_INSTANCE  USART2
#define BENCH_UART_TX_PORT   GPIOA
#define BENCH_UART_TX_PIN    GPIO_PIN_2
#define BENCH_UART_RX_PORT   GPIOA
#define BENCH_UART_RX_PIN    GPIO_PIN_3
#define BENCH_UART_AF        GPIO_AF7_USART2
#define BENCH_UART_BAUD      115200u

/* Horloge fiable pour le CAN ? Renseigné à l'exécution par clock.c. */
#define BENCH_CLOCK_FIX_HINT \
    "Verifier que le ST-LINK fournit bien le MCO 8 MHz (UM1724, SB50/SB54/SB55)."

#endif /* BENCH_BOARD_H */
